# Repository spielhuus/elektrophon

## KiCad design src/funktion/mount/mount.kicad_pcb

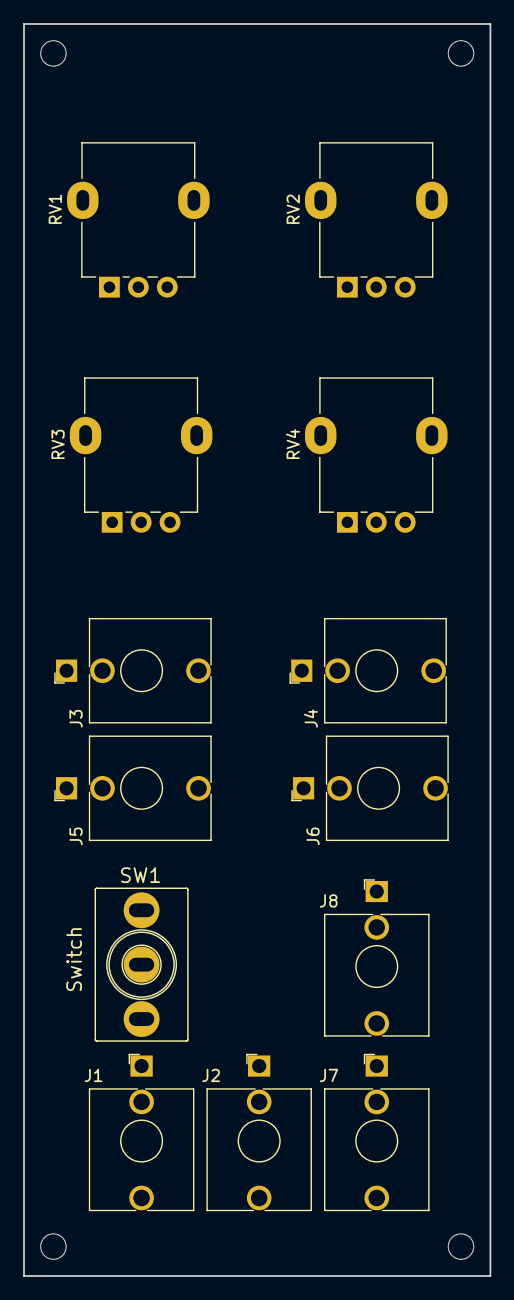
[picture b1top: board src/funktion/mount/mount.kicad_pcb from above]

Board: 2 copper layers, 40.3 x 108.2 mm, 17 parts (0 on the bottom side), 2 nets, no tracks yet.

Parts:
H1, H2, H3, H4: MountingHole; MountingHole_2.2mm_M2
J1, J2, J3, J4, J5, J6, J7, J8: PJ398SM; Jack_3.5mm_WQP-PJ398SM_Vertical
RV1, RV2, RV3, RV4: 10k; Potentiometer_Alpha_RD901F-40-00D_Single_Vertical
SW1: Switch; SPDT_KIT

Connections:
/RELEASE: J4.T, J6.T
GND: J1.S, J2.S, J3.S, J4.S, J5.S, J6.S, J7.S, J8.S

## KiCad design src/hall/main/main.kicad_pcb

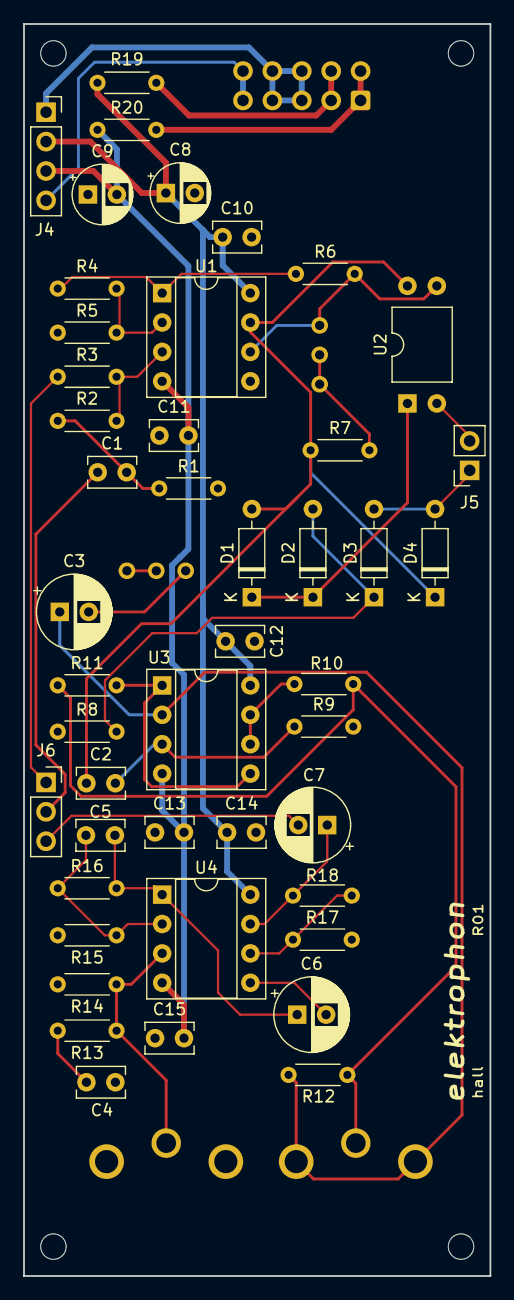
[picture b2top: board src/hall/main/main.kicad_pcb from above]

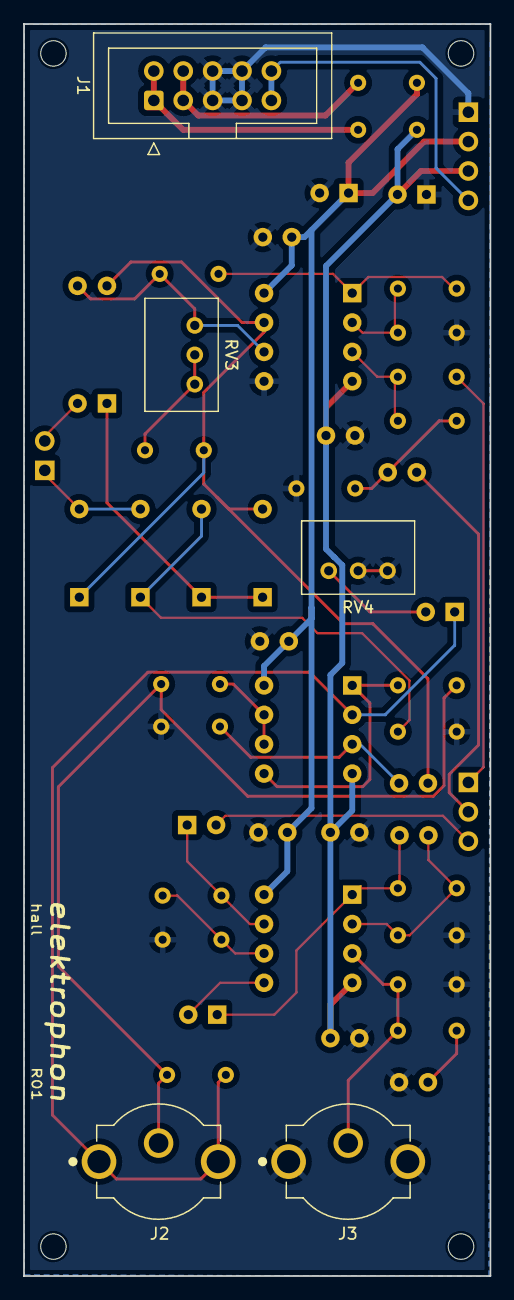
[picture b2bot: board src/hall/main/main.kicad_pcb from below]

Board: 2 copper layers, 40.3 x 108.2 mm, 55 parts (5 on the bottom side), 33 nets.

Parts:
C1, C2, C10, C11, C12, C13, C14, C15: 100n; C_Rect_L4.0mm_W2.5mm_P2.50mm
C3, C6, C7: 10u (NP); CP_Radial_D6.3mm_P2.50mm
C4: 10n; C_Rect_L4.0mm_W2.5mm_P2.50mm
C5: 1n; C_Rect_L4.0mm_W2.5mm_P2.50mm
C8, C9: 10u; CP_Radial_D5.0mm_P2.50mm
D1, D2, D3, D4: 1N4148; D_DO-35_SOD27_P7.62mm_Horizontal
H1: H1; MountingHole_2.2mm_M2
H2: H2; MountingHole_2.2mm_M2
H3: H3; MountingHole_2.2mm_M2
H4: H4; MountingHole_2.2mm_M2
J1: IDC_Header; IDC-Header_2x05_P2.54mm_Vertical
J2: RCJ-021; CUI_RCJ-026
J3: RCJ-022; CUI_RCJ-026
J4: 01x04 Female; PinSocket_1x04_P2.54mm_Vertical
J5: 01x02 Female; PinSocket_1x02_P2.54mm_Vertical
J6: 01x03 Female; PinSocket_1x03_P2.54mm_Vertical
R1, R5: 100k; R_Axial_DIN0204_L3.6mm_D1.6mm_P5.08mm_Horizontal
R2, R3, R4, R6, R9, R13: 10k; R_Axial_DIN0204_L3.6mm_D1.6mm_P5.08mm_Horizontal
R7: 1k; R_Axial_DIN0204_L3.6mm_D1.6mm_P5.08mm_Horizontal
R8, R15: 100; R_Axial_DIN0204_L3.6mm_D1.6mm_P5.08mm_Horizontal
R10, R11, R19, R20: 10; R_Axial_DIN0204_L3.6mm_D1.6mm_P5.08mm_Horizontal
R12: 12k; R_Axial_DIN0204_L3.6mm_D1.6mm_P5.08mm_Horizontal
R14: 220k; R_Axial_DIN0204_L3.6mm_D1.6mm_P5.08mm_Horizontal
R16: 22k; R_Axial_DIN0204_L3.6mm_D1.6mm_P5.08mm_Horizontal
R17: 2.2k; R_Axial_DIN0204_L3.6mm_D1.6mm_P5.08mm_Horizontal
R18: 4.7k; R_Axial_DIN0204_L3.6mm_D1.6mm_P5.08mm_Horizontal
RV3: 100k; Potentiometer_Bourns_3299W_Vertical
RV4: 10k; Potentiometer_Bourns_3299W_Vertical
U1, U3, U4: NE5532; DIP-8_W7.62mm_Socket
U2: type="X" model="LCR-0202" lib=""; DIP-4_W10.16mm

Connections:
+5V: J1.9, J1.10, J4.4
+15V: C8.1, C10.1, C12.1, C14.1, J4.2, R19.2, U1.8 (V+), U3.8 (V+), U4.8 (V+)
-15V: C9.2, C11.2, C13.2, C15.2, J4.3, R20.1, U1.4 (V-), U3.4 (V-), U4.4 (V-)
/FB2: J6.1, R3.2
/IN: C1.1, J6.2
/LED1: D3.2 (A), D4.2 (A), J5.1
/LED2: J5.2, U2.2 (+)
/REVERB: C7.2, J6.3
/VN: J1.1, J1.2, R20.2
/VP: J1.3, J1.4, R19.1
GND: C4.2, C8.2, C9.1, C10.2, C11.1, C12.2, C13.1, C14.2, C15.1, J1.5, J1.6, J1.7, J1.8, J3.2 (Ext), J4.1, R1.2, R5.2, R8.2, R9.2, R14.2, R15.2, R17.2, RV4.2, RV4.3, U1.5 (+)
unnamed: C1.2, R1.1, R2.1
unnamed: C3.2, RV4.1
unnamed: C4.1, R13.2
unnamed: C5.2, C6.1, R16.2, U4.1
unnamed: C7.1, R18.2, U4.7
unnamed: C2.1, D1.2 (A), D4.1 (K), R7.1, U1.7, U2.4
unnamed: D1.1 (K), D2.1 (K), U2.1 (-)
unnamed: D2.2 (A), D3.1 (K), R8.1
unnamed: C3.1, J2.2 (Ext), R12.1, U3.2 (-)
unnamed: J2.1 (In), R10.2, R11.1, R12.2
unnamed: J3.1 (In), R13.1, R14.1, U4.3 (+)
unnamed: R4.1, R6.1, U1.1
unnamed: R7.2, RV3.1, RV3.2
unnamed: R2.2, R3.1, U1.3 (+)
unnamed: R4.2, R5.1, U1.2 (-)
unnamed: R6.2, RV3.3, U1.6 (-), U2.3
unnamed: C2.2, R9.1, U3.3 (+)
unnamed: R11.2, U3.1, U3.5 (+)
unnamed: R10.1, U3.6 (-), U3.7
unnamed: C5.1, R15.1, R16.1, U4.2 (-)
unnamed: C6.2, U4.5 (+)
unnamed: R17.1, R18.1, U4.6 (-)

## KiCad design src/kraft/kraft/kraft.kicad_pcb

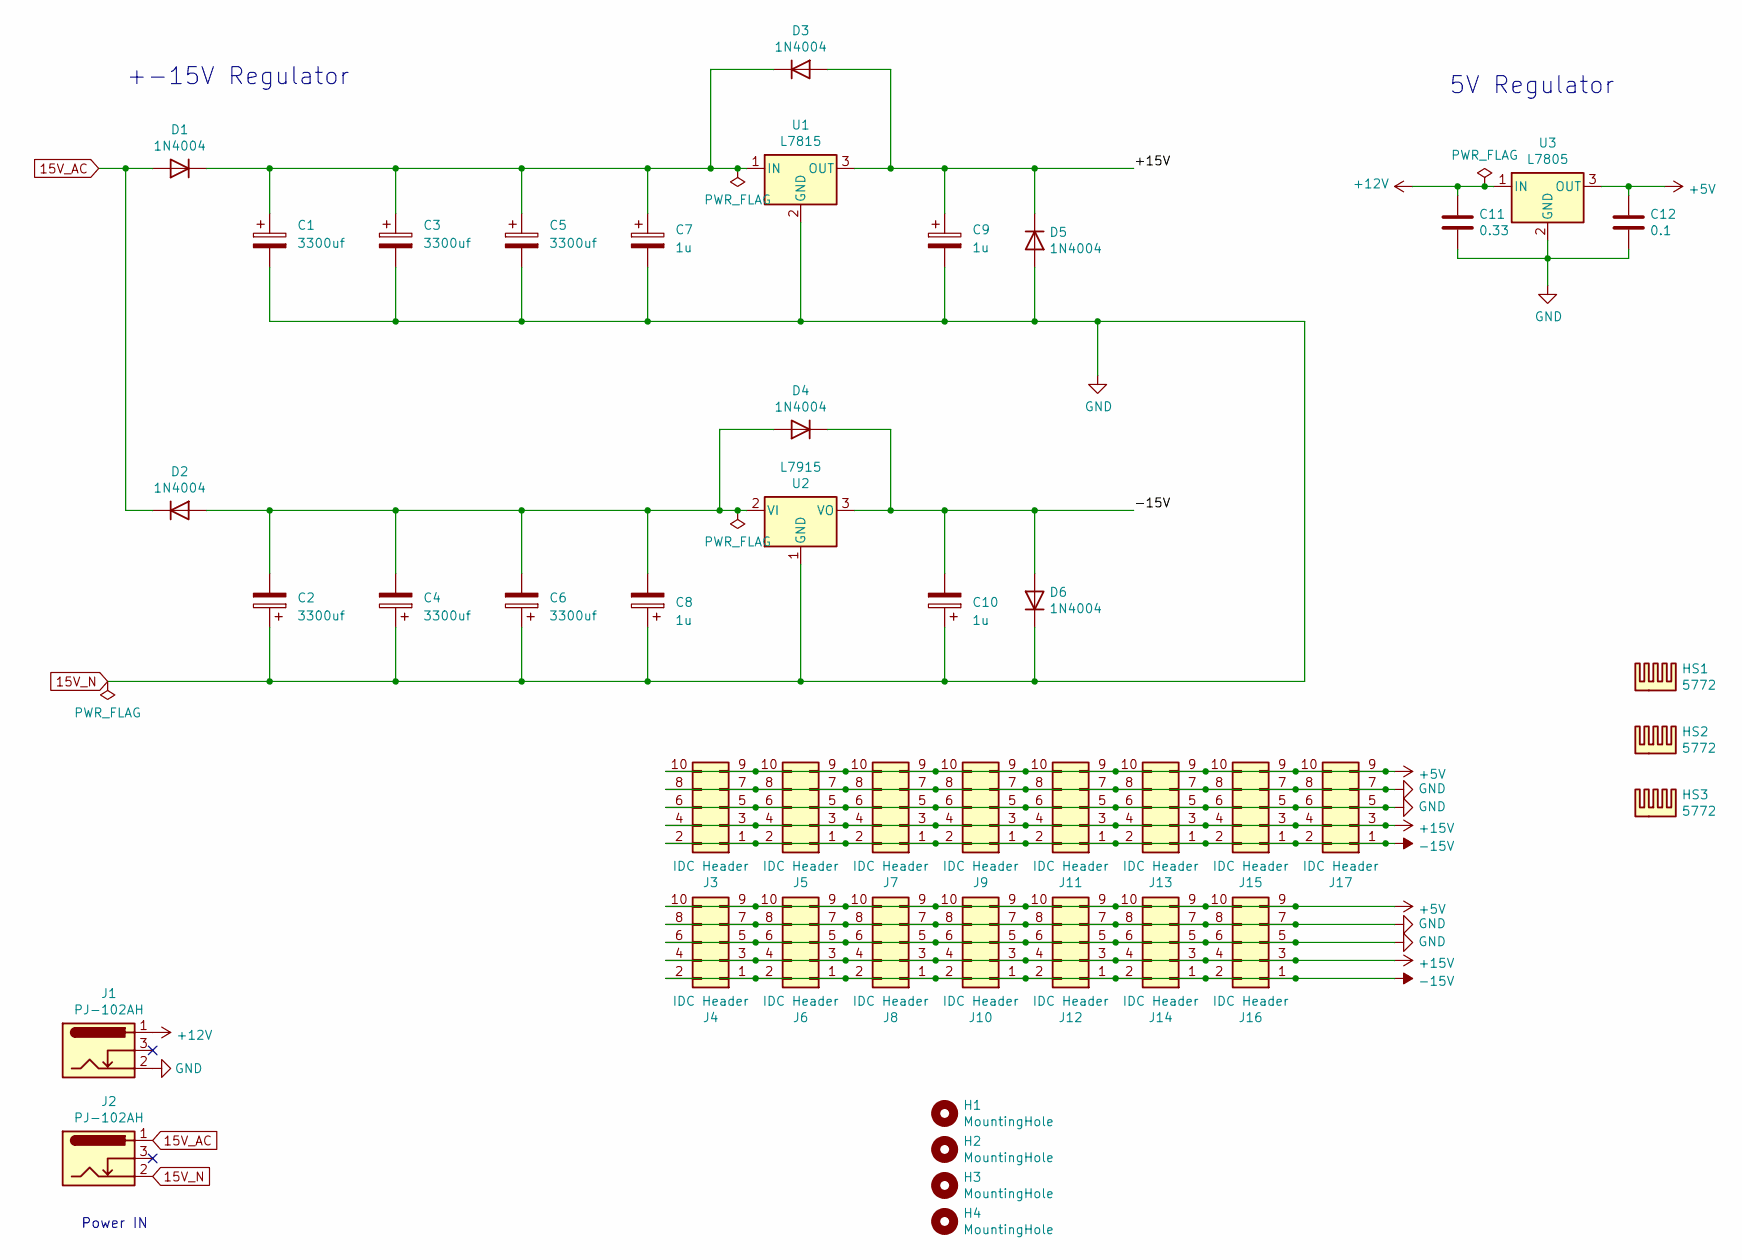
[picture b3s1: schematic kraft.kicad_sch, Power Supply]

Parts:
C1, C2, C3, C4, C5, C6: 3300uf; CP_Radial_D12.5mm_P5.00mm
C7, C8, C9, C10: 1u; CP_Radial_D5.0mm_P2.00mm
C11: 0.33; C_Disc_D4.7mm_W2.5mm_P5.00mm
C12: 0.1; C_Disc_D4.7mm_W2.5mm_P5.00mm
D1, D2, D3, D4, D5, D6: 1N4004; D_DO-41_SOD81_P10.16mm_Horizontal
H1, H2, H3, H4: MountingHole; MountingHole_2.2mm_M2
HS1, HS2, HS3: 5772
J1, J2: PJ-102AH; BarrelJack_CUI_PJ-102AH_Horizontal
J3, J4, J5, J6, J7, J8, J9, J10, J11, J12, J13, J14, J15, J16, J17: IDC Header; IDC-Header_2x05_P2.54mm_Vertical
U1: L7815; TO-220-3_Vertical
U2: L7915; TO-220-3_Vertical
U3: L7805; TO-220-3_Vertical

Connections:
15V_AC: D1.2 (A), D2.1 (K), J2.1
15V_N: C1.2, C2.1, C3.2, C4.1, C5.2, C6.1, C7.2, C8.1, C9.2, C10.1, C11.2, C12.2, D5.2 (A), D6.1 (K), J1.2, J2.2, J3.5, J3.6, J3.7, J3.8, J4.5, J4.6, J4.7, J4.8, J5.5, J5.6, J5.7, J5.8, J6.5, J6.6, J6.7, J6.8, J7.5, J7.6, J7.7, J7.8, J8.5, J8.6, J8.7, J8.8, J9.5, J9.6, J9.7, J9.8, J10.5, J10.6, J10.7, J10.8, J11.5, J11.6, J11.7, J11.8, J12.5, J12.6, J12.7, J12.8, J13.5, J13.6, J13.7, J13.8, J14.5, J14.6, J14.7, J14.8, J15.5, J15.6, J15.7, J15.8, J16.5, J16.6, J16.7, J16.8, J17.5, J17.6, J17.7, J17.8, U1.2 (GND), U2.1 (GND), U3.2 (GND)
+5V: C12.1, J3.9, J3.10, J4.9, J4.10, J5.9, J5.10, J6.9, J6.10, J7.9, J7.10, J8.9, J8.10, J9.9, J9.10, J10.9, J10.10, J11.9, J11.10, J12.9, J12.10, J13.9, J13.10, J14.9, J14.10, J15.9, J15.10, J16.9, J16.10, J17.9, J17.10, U3.3 (OUT)
+12V: C11.1, J1.1, U3.1 (IN)
+15V: C9.1, D3.2 (A), D5.1 (K), J3.3, J3.4, J4.3, J4.4, J5.3, J5.4, J6.3, J6.4, J7.3, J7.4, J8.3, J8.4, J9.3, J9.4, J10.3, J10.4, J11.3, J11.4, J12.3, J12.4, J13.3, J13.4, J14.3, J14.4, J15.3, J15.4, J16.3, J16.4, J17.3, J17.4, U1.3 (OUT)
-15V: C10.2, D4.1 (K), D6.2 (A), J3.1, J3.2, J4.1, J4.2, J5.1, J5.2, J6.1, J6.2, J7.1, J7.2, J8.1, J8.2, J9.1, J9.2, J10.1, J10.2, J11.1, J11.2, J12.1, J12.2, J13.1, J13.2, J14.1, J14.2, J15.1, J15.2, J16.1, J16.2, J17.1, J17.2, U2.3 (VO)
unnamed: C1.1, C3.1, C5.1, C7.1, D1.1 (K), D3.1 (K), U1.1 (IN)
unnamed: C2.2, C4.2, C6.2, C8.2, D2.2 (A), D4.2 (A), U2.2 (VI)

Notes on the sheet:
Power IN
+-15V Regulator
5V Regulator

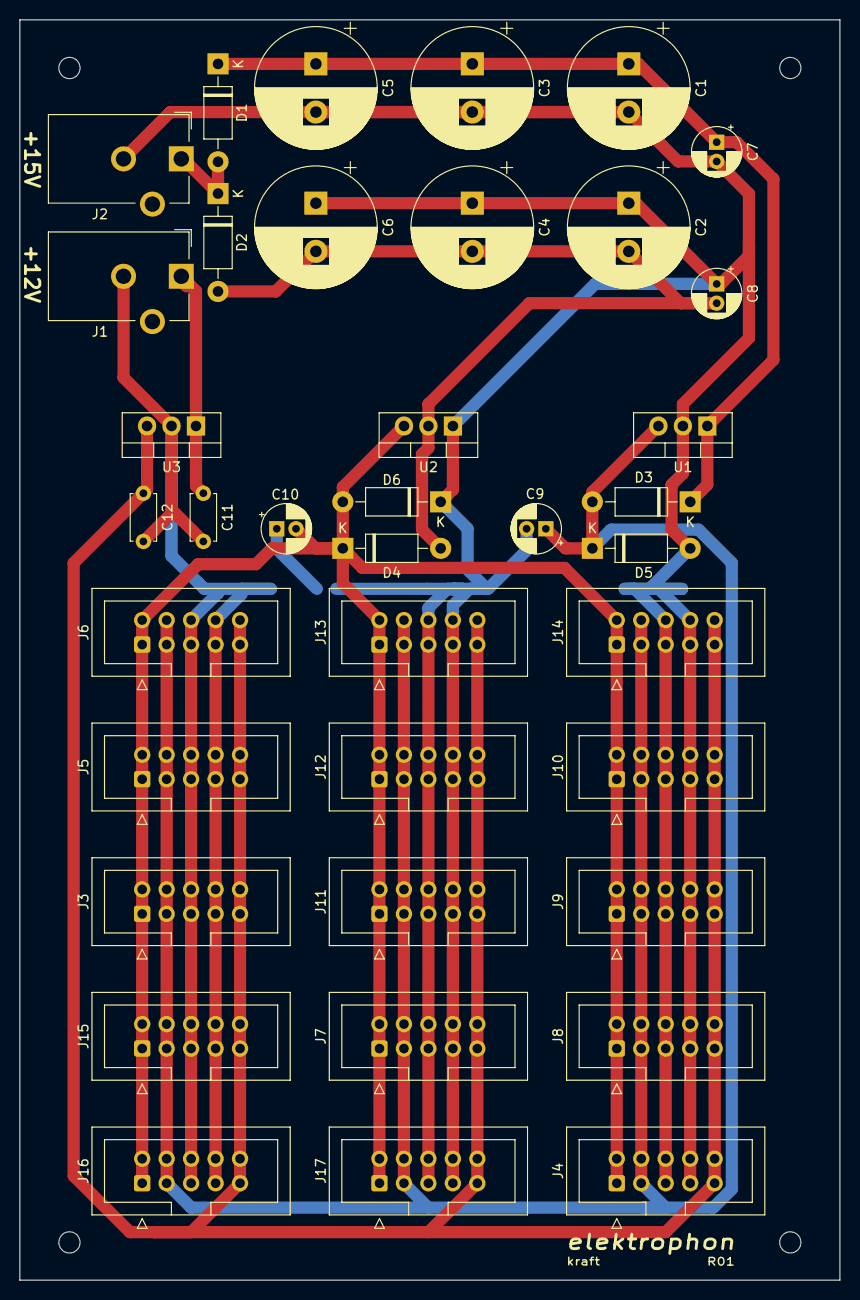
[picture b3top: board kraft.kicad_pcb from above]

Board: 2 copper layers, 85.1 x 130.8 mm, 42 parts (0 on the bottom side), 8 nets.

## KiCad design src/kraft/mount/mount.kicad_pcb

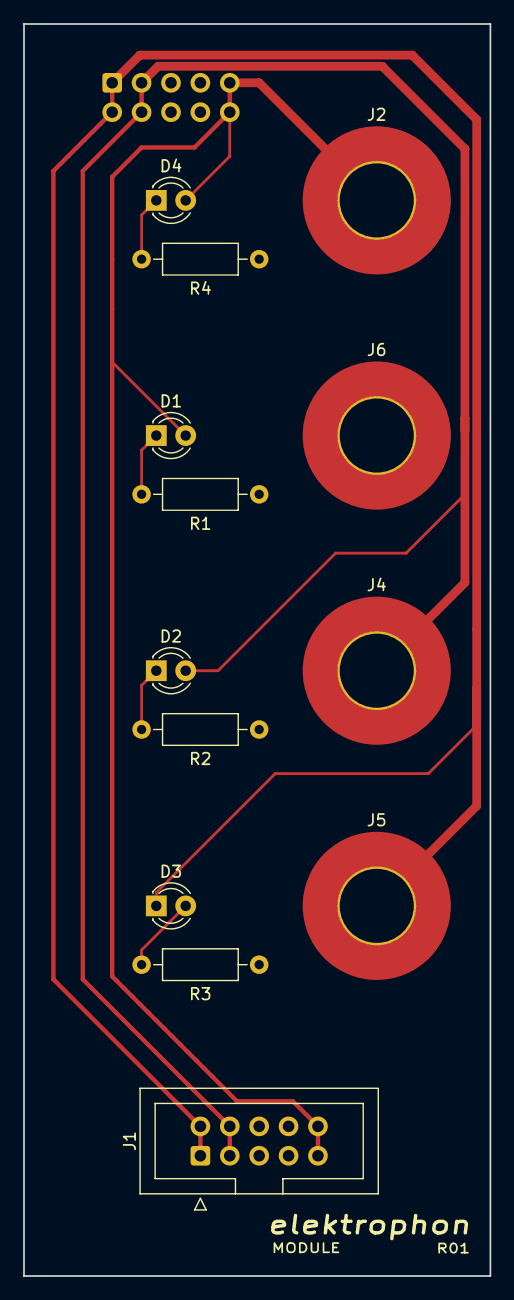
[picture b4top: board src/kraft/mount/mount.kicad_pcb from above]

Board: 2 copper layers, 40.3 x 108.2 mm, 14 parts (1 on the bottom side), 8 nets.

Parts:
D1, D2, D3, D4: LED; LED_D3.0mm
J1, J3: IDC Header; IDC-Header_2x05_P2.54mm_Vertical
J2, J4, J5, J6: CT2224; MountingHole_6.4mm_M6_Pad_TopBottom
R1: 1k2; R_Axial_DIN0207_L6.3mm_D2.5mm_P10.16mm_Horizontal
R2, R3: 6k8; R_Axial_DIN0207_L6.3mm_D2.5mm_P10.16mm_Horizontal
R4: 2k2; R_Axial_DIN0207_L6.3mm_D2.5mm_P10.16mm_Horizontal

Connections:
+5V: D1.2, D4.2, J1.9, J1.10, J2.1, J3.9, J3.10
+15V: D2.2, J1.3, J1.4, J3.3, J3.4, J4.1
-15V: D3.1, J1.1, J1.2, J3.1, J3.2, J5.1
GND: J1.5, J1.6, J1.7, J1.8, J3.5, J3.6, J3.7, J3.8, J6.1, R1.2, R2.2, R3.2, R4.2
unnamed: D1.1, R1.1
unnamed: D2.1, R2.1
unnamed: D3.2, R3.1
unnamed: D4.1, R4.1

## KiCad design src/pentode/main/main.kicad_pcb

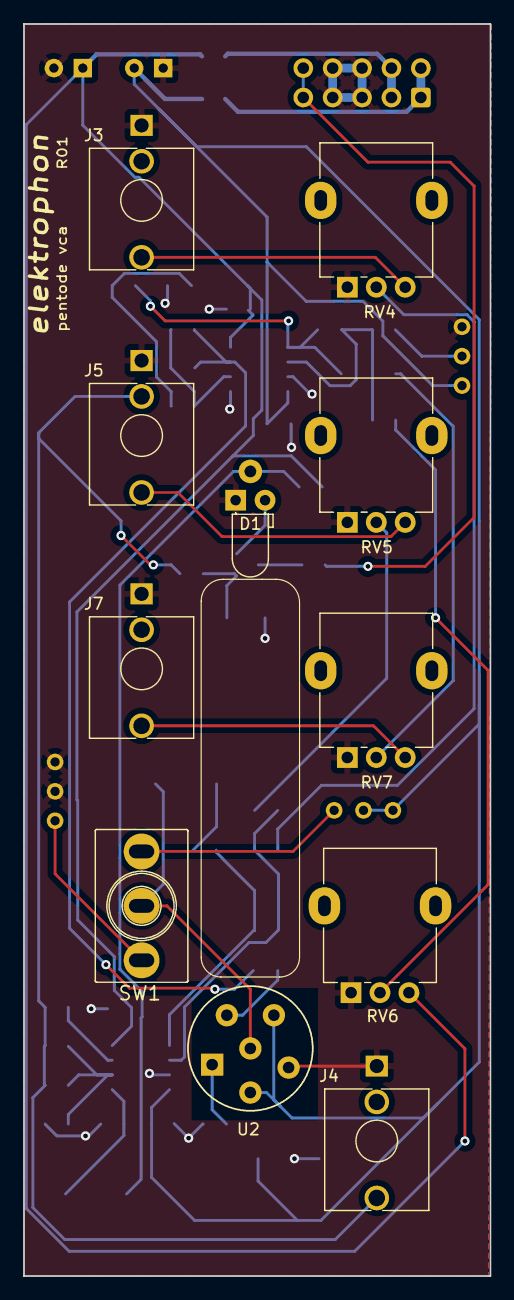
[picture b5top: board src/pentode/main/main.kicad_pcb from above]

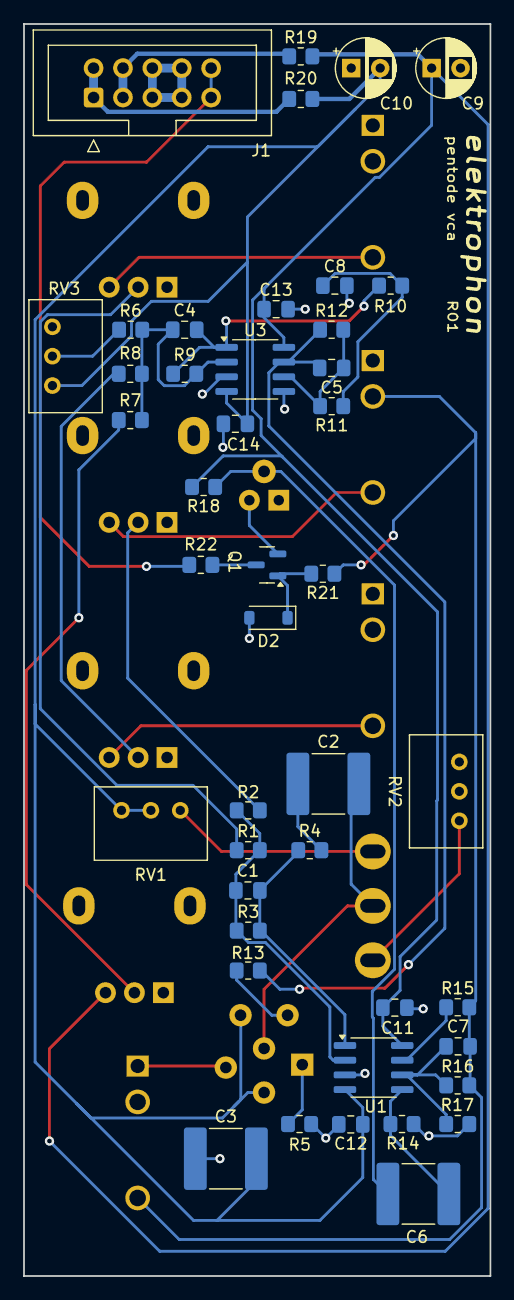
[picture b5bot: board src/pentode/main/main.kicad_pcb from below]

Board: 2 copper layers, 40.3 x 108.2 mm, 55 parts (44 on the bottom side), 35 nets.

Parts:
C1, C4, C5, C7: 22p (C0G); C_0805_2012Metric_Pad1.18x1.45mm_HandSolder
C2, C6: 470n (C0G); C_2220_5750Metric_Pad1.97x5.40mm_HandSolder
C3: 47u; C_2220_5750Metric_Pad1.97x5.40mm_HandSolder
C8: 0.1u; C_0805_2012Metric_Pad1.18x1.45mm_HandSolder
C9, C10: 10u; CP_Radial_D5.0mm_P2.50mm
C11, C12, C13, C14: 100n; C_0805_2012Metric_Pad1.18x1.45mm_HandSolder
D1: LED (Red); LED_D3.0mm_Horizontal_O1.27mm_Z2.0mm
D2: 1N4148W; D_SOD-123
J1: IDC_Header; IDC-Header_2x05_P2.54mm_Vertical
J3, J4, J5, J7: PJ398SM; Jack_3.5mm_WQP-PJ398SM_Vertical
Q1: MMBT3904; SOT-23
R1, R2, R3: 20k; R_0805_2012Metric_Pad1.20x1.40mm_HandSolder
R4, R16: 2.2k; R_0805_2012Metric_Pad1.20x1.40mm_HandSolder
R5: 750 (0.5W); R_0805_2012Metric_Pad1.20x1.40mm_HandSolder
R6, R7, R8, R11, R13, R18, R21: 100k; R_0805_2012Metric_Pad1.20x1.40mm_HandSolder
R9, R12: 220k; R_0805_2012Metric_Pad1.20x1.40mm_HandSolder
R10: 10k; R_0805_2012Metric_Pad1.20x1.40mm_HandSolder
R14: 33k; R_0805_2012Metric_Pad1.20x1.40mm_HandSolder
R15: 330; R_0805_2012Metric_Pad1.20x1.40mm_HandSolder
R17: 1k; R_0805_2012Metric_Pad1.20x1.40mm_HandSolder
R19, R20: 10; R_0805_2012Metric_Pad1.20x1.40mm_HandSolder
R22: 5.1k; R_0805_2012Metric_Pad1.20x1.40mm_HandSolder
RV1, RV3: 100k; Potentiometer_Bourns_3299W_Vertical
RV2: 1meg; Potentiometer_Bourns_3299W_Vertical
RV4, RV5, RV6: A50k; Potentiometer_Alpha_RD901F-40-00D_Single_Vertical
RV7: 50k; Potentiometer_Alpha_RD901F-40-00D_Single_Vertical
SW1: Switch; SPDT_KIT
U1: TL072; SOIC-8_3.9x4.9mm_P1.27mm
U2: 1J24B
U3: LM358; SOIC-8_3.9x4.9mm_P1.27mm

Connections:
+5V: J1.9, J1.10, R22.2
+15V: C9.1, C11.1, C13.1, R18.2, R19.2, RV6.3, U1.8 (V+), U3.8 (V+)
-15V: C3.2, C10.2, C12.2, C14.2, R20.1, RV1.2, RV1.3, RV3.3, U1.4 (V-), U2.2 (CATH2), U2.4 (SUPPR), U3.4 (V-)
/CV1: R8.2, RV7.2
/GAIN: R7.2, RV6.2
/IN: R1.1, RV4.2
/OUT: C7.2, J4.T, J5.TN, R15.2, R16.2, R21.1
/RES: R2.2, RV5.2
/VN: J1.1, J1.2, R20.2
/VP: J1.3, J1.4, R19.1
GND: C3.1, C8.2, C9.2, C10.1, C11.2, C12.1, C13.2, C14.1, D1.1 (K), D2.2 (A), J1.5, J1.6, J1.7, J1.8, J3.S, J4.S, J5.S, J7.S, R5.2, R14.2, R17.2, RV2.2, RV2.3, RV3.1, RV4.1, RV5.1, RV6.1, RV7.1, U1.3 (+), U2.3 (BODY), U3.3 (+), U3.5 (+)
unnamed: C1.2, R3.1, R4.1, U1.1
unnamed: C2.1, R4.2
unnamed: C4.2, R9.1, R10.1, U3.1
unnamed: C5.2, R12.1, R13.1, U3.7
unnamed: C8.1, R10.2, R11.1
unnamed: D1.2 (A), Q1.2 (E)
unnamed: D2.1 (K), Q1.1 (B), R21.2
unnamed: J3.T, RV4.3
unnamed: J5.T, RV5.3
unnamed: J7.T, RV7.3
unnamed: Q1.3 (C), R22.1
unnamed: R6.1, RV3.2
unnamed: R15.1, U1.7
unnamed: RV2.1, SW1.1 (A)
unnamed: C2.2, SW1.2 (B), U2.6 (GRID)
unnamed: RV1.1, SW1.3 (C)
unnamed: C1.1, R1.2, R2.1, R3.2, U1.2 (-)
unnamed: C6.2, R14.1, U1.5 (+)
unnamed: C7.1, R16.1, R17.1, U1.6 (-)
unnamed: C6.1, R18.1, U2.7 (ANODE)
unnamed: R5.1, U2.1 (CATH1)
unnamed: R13.2, U2.5 (SCREEN)
unnamed: C4.1, R6.2, R7.1, R8.1, R9.2, U3.2 (-)
unnamed: C5.1, R11.2, R12.2, U3.6 (-)

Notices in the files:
src/funktion/mount/mount.kicad_pcb:
License CC BY 4.0 - Attribution 4.0 International
